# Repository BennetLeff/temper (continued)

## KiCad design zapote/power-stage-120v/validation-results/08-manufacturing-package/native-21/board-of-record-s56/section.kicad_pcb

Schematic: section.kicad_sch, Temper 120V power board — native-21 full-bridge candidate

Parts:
BR1: GBJ2510-F; Diode_Bridge_GBJ2510
C1, C2: R463N410050N1K; KEMET_R463N410000N1M_P22.50_ReviewOnly
C3, C4: DE1E3RA222MJ4BH01F; Murata_DE1E3RA222MA4BP01F_P10.0_Pad1.5_ReviewOnly
C5, C6: B32676G1905K000; TDK_B32656G0275J000_4Pin_P37.50_P20.30_ReviewOnly
C7, C14, C25, C28, C29, C32, C34, C35, C36, C37, C44, C45, C46, C47, C48, C49, C54, C61, C65, C70, C74, C75, C80, C81, C82, C87, C89, C131, C133, C134, C135, C139, C144, C153, C154, C155, C156, C157, C158, C159, C160, C161, C163, C168, C169, C170, C171, C172, C173, C174, C175, C176, C177, C178: CC0603KRX7R9BB104; C_0603_1608Metric
C8, C10, C15, C17: CC0805KRX7R9BB104; C_0805_2012Metric
C9, C16, C24, C26, C90, C91, C92, C93, C94, C95, C96, C97, C98, C99, C100, C102, C103, C104, C106, C107, C108, C132, C136, C140: CL32B106KBJNNNE; C_1210_3225Metric
C11, C18: GRM21BZ71E106KE15L; C_0805_2012Metric
C12, C13, C19, C20: CC1206JKNPOCBN102; C_1206_3216Metric
C21, C22, C23, C151, C152: B32643H8104J000; Bank_Film_DualPitch_P22.5_P27.5_Radial
C27, C31, C33, C66, C67, C68, C69, C76, C77, C78, C79, C83, C84, C85, C86, C164, C165, C166: C0603C102J5GACTU; C_0603_1608Metric
C30, C167: CL10C101JB8NNNC; C_0603_1608Metric
C38, C39, C40, C41: B32652A0104K000; TDK_B32652A0104K000_P15.00_ReviewOnly
C42, C43: GRM31C5C1H104JA01L; C_1206_3216Metric
C50, C51, C52, C53, C57, C58, C59, C60, C64: GRM188R71E105KA12D; C_0603_1608Metric
C55, C56, C62, C63: GRM1885C1H472JA01D; C_0603_1608Metric
C71, C72, C105, C109, C162: CL10C331JB8NNNC; C_0603_1608Metric
C110, C111, C112, C113, C114, C115, C116, C117, C118, C119, C120, C121, C122, C123, C124, C125: CL05B104KB54PNC; C_0402_1005Metric
C126, C127, C128, C129: 6SVPC220MV; CP_Elec_6.3x5.9
C145, C146, C147, C148, C149, C150: CL21B105KBFNNNE; C_0805_2012Metric
D3, D17: 30KPA150CA; P600_Axial_P12.70mm_ReviewOnly
D4, D5: BAS116H,115; D_SOD-123F
D6, D7, D8, D9: PMEG6030EP,115; D_SOD-128
D18, D19, D20: BAT54S-7-F; SOT-23
F1: KLDR025.TXP; Fuseholder_Clip-10.3x38mm_Littelfuse_125_Inline_P41.76x10.8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
F2: 3403.0279.23; Fuse_Schurter_UMT-H_15.4x5.35mm
J1: 1714971; Phoenix_MKDS-5-2-9.52_1714971
J2, J5: 7466004R; Wuerth_REDCUBE-SMT_WP-SMBU_7466004R
J3, J11: B2P3-VH(LF)(SN); JST_VH_B2P3-VH_1x02_P7.92mm_Vertical
J4: 0430451612; Molex_Micro-Fit_3.0_43045-1612_2x08_P3.00mm_Vertical
J6: 1704004; Phoenix_KDS3_1704004_1Pos_2Pin_ReviewOnly
L1: B82726S2243A020; B82726S2_ReviewOnly
PS2: MPM-20-24; Converter_ACDC_MeanWell_IRM-20-xx_THT
Q2, Q3, Q5, Q6: IPW65R018CFD7; TO-247-3_Vertical
R1, R2: 1206W4F1003T5E; R_1206_3216Metric
R3, R4, R146: RC1206FR-07220KL; R_1206_3216Metric
R5: CSS2H-2512R-1L00F; R_Shunt_Bourns_CSS2H-2512_Kelvin
R6, R14: 0603WAF1000T5E; R_0603_1608Metric
R7, R15, R62, R128, R135, R136, R138, R140, R142: 0603WAF1003T5E; R_0603_1608Metric
R9, R17, R133: RT0603BRD0749K9L; R_0603_1608Metric
R10, R12, R18, R20: PS122WF680JT4E; R_2512_6332Metric
R11, R13, R19, R21, R73, R76, R91, R109, R124: 0603WAF1002T5E; R_0603_1608Metric
R22, R23, R24, R25, R26, R27, R28, R29: RC1206FR-07470KL; R_1206_3216Metric
R30: RT0603BRD0715K8L; R_0603_1608Metric
R31: 0603WAF5601T5E; R_0603_1608Metric
R32, R36, R49, R50, R78, R80, R82, R84, R96, R98, R100, R102, R111, R113, R115, R117: RT0603BRD0710KL; R_0603_1608Metric
R33: RT0603BRD077K5L; R_0603_1608Metric
R34: RT0603BRD0716KL; R_0603_1608Metric
R35, R44, R45, R61, R86, R88, R93, R104, R106, R119, R121: RT0603BRD0711KL; R_0603_1608Metric
R37: RT0603BRD07140KL; R_0603_1608Metric
R38: 0603WAF0000T5E; R_0603_1608Metric
R39: RC1206FR-073RL; R_1206_3216Metric
R40, R41: RT0603BRD071KL; R_0603_1608Metric
R42: 1206W4F1001T5E; R_1206_3216Metric
R43, R46: RT0603BRD072K21L; R_0603_1608Metric
R47, R134: 0603WAF1001T5E; R_0603_1608Metric
R48: RT0603BRD07105KL; R_0603_1608Metric
R51, R52, R55, R56: RL1206FR-070R68L; R_1206_3216Metric
R53, R54, R57, R58: 1206W4F100KT5E; R_1206_3216Metric
R59, R63, R65: RC1206FR-072K2L; R_1206_3216Metric
R67, R68, R69, R70: RC1206FR-0716K5L; R_1206_3216Metric
R71, R72, R74, R75, R131: ERJ-PA3F4991V; R_0603_1608Metric
R77, R95, R110: RT0603BRD076K2L; R_0603_1608Metric
R79, R97, R112: RT0603BRD074K42L; R_0603_1608Metric
R81, R99, R114: RT0603BRD07750RL; R_0603_1608Metric
R83, R101, R116: RT0603BRD072K94L; R_0603_1608Metric
R85, R103, R118: RT0603BRD0790K9L; R_0603_1608Metric
R87, R105, R120: RT0603BRD07104KL; R_0603_1608Metric
R92, R94, R144: RT0603BRD0763K4L; R_0603_1608Metric
R125: 0603WAF3302T5E; R_0603_1608Metric
R127, R129, R137, R139, R141, R143: 0603WAF2702T5E; R_0603_1608Metric
R130: AC05000001507JAC00; R_Axial_Vishay_AC05_D7.5mm_P5.08mm_Vertical
R132: 0603WAF2200T5E; R_0603_1608Metric
R145: TNPW060311K7BEEA; R_0603_1608Metric
RV1: TMOV20RP175E; TMOV20RP_ReviewOnly
T1: CST3015-200ED; CST3015
U1, U2: 2EDR8259XXUMA1; SOIC16W_Isolated
U3, U37, U38, U39: TPS70950QDBVRQ1; SOT-23-5
U4: AMC1311BDWVR; SOIC-8_7.5x5.85mm_P1.27mm
U5: LM4050AEM3-2.5/NOPB; SOT-23
U6, U7, U10, U11, U12: TLV3201AIDBVR; SOT-23-5
U8: SN74LVC1G10DBVR; SOT-23-6
U9, U32: CA-IS3720HW; SOIC16W_DW0016B_HV
U13: SN74LVC1G332DBVR; SOT-23-6
U14: TPS3700DDCR; SOT-23-6
U15, U24, U40: SN74LVC1G17DBVR; SOT-23-5
U16, U18, U20: TLVH431BQDBZR; SOT-23
U17, U19, U21: TL431BQDBZR; SOT-23
U22, U23: SN74LVC1G00DBVR; SOT-23-5
U26: TPS7A4700RGWR; Texas_RGW0020A_VQFN-20-1EP_5x5mm_P0.65mm_EP3.15x3.15mm
U29, U30, U31: LM2901BIDR; SOIC-14_3.9x8.7mm_P1.27mm
U36: VOL628A-2X001T; VOL628A_LSOP4_ReviewOnly
U41, U42: R24C2T25/R-R; RECOM_SSOP-36_7.5x12.83mm_P0.65mm_ReviewOnly
U43, U44: ISO6721FBDR; SOIC-8_3.9x4.9mm_P1.27mm
U45, U46: SN74LVC1G132DBVR; SOT-23-5

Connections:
ac_l_in: F1.1 (p1), J1.1 (p1)
ac_n_in: C1.2 (p2), J1.2 (p2), L1.2 (p2), R2.2 (p2), RV1.2 (p2)
bias_good: R146.1 (p1), U22.2 (p2), U23.2 (p2), U40.4 (Y); also elsewhere on the board
bias_good_j4: J4.1 (p1), R146.2 (p2)
bias_ha-en: R62.2 (p2), R127.1 (p1), U41.4 (p4)
bias_ha-fbm: C71.1 (p1), R92.2 (p2), R93.1 (p1), U41.33 (p33), U41.34 (p34)
bias_ha-outa_nc: U43.2 (p2)
bias_ha.iso-p3: U41.3 (p3)
bias_ha.iso-p32: U41.32 (p32)
bias_ha.monitor-good: R109.2 (p2), U30.1 (OUT2), U30.2 (OUT1), U30.13 (OUT4), U30.14 (OUT3), U43.3 (p3)
bias_ha.monitor-halfref: R97.2 (p2), R98.1 (p1), U30.5 (IN1+), U30.6 (IN2-), U30.8 (IN3-), U30.11 (IN4+)
bias_ha.monitor-ldo_en: R140.2 (p2), R141.1 (p1), U38.3 (EN)
bias_ha.monitor-ov: C77.1 (p1), R101.2 (p2), R102.1 (p1), U30.4 (IN1-); also elsewhere on the board
bias_ha.monitor-ref: R63.2 (p2), R97.1 (p1), U19.1 (K), U19.2 (REF)
bias_ha.monitor-spanov: C79.1 (p1), R105.2 (p2), R106.1 (p1), U30.10 (IN4-); also elsewhere on the board
bias_ha.monitor-spanuv: C78.1 (p1), R103.2 (p2), R104.1 (p1), U30.9 (IN3+); also elsewhere on the board
bias_ha.monitor-uv: C76.1 (p1), R99.2 (p2), R100.1 (p1), U30.7 (IN2+); also elsewhere on the board
bias_ha.monitor-v5: C136.1 (p1), C157.1 (p1), R109.1 (p1), U38.5 (OUT), U43.1 (p1)
bias_ha.monitor.ldo5-nc: U38.4 (NC)
bias_ha.split-fb: R95.2 (p2), R96.1 (p1), U18.1 (REF)
bias_hb-en: R128.2 (p2), R129.1 (p1), U42.4 (p4)
bias_hb-fbm: C72.1 (p1), R61.1 (p1), R94.2 (p2), U42.33 (p33), U42.34 (p34)
bias_hb-outa_nc: U44.2 (p2)
bias_hb.iso-p3: U42.3 (p3)
bias_hb.iso-p32: U42.32 (p32)
bias_hb.monitor-good: R124.2 (p2), U31.1 (OUT2), U31.2 (OUT1), U31.13 (OUT4), U31.14 (OUT3), U44.3 (p3)
bias_hb.monitor-halfref: R112.2 (p2), R113.1 (p1), U31.5 (IN1+), U31.6 (IN2-), U31.8 (IN3-), U31.11 (IN4+)
bias_hb.monitor-ldo_en: R142.2 (p2), R143.1 (p1), U39.3 (EN)
bias_hb.monitor-ov: C84.1 (p1), R116.2 (p2), R117.1 (p1), U31.4 (IN1-); also elsewhere on the board
bias_hb.monitor-ref: R65.2 (p2), R112.1 (p1), U21.1 (K), U21.2 (REF)
bias_hb.monitor-spanov: C86.1 (p1), R120.2 (p2), R121.1 (p1), U31.10 (IN4-); also elsewhere on the board
bias_hb.monitor-spanuv: C85.1 (p1), R118.2 (p2), R119.1 (p1), U31.9 (IN3+); also elsewhere on the board
bias_hb.monitor-uv: C83.1 (p1), R114.2 (p2), R115.1 (p1), U31.7 (IN2+); also elsewhere on the board
bias_hb.monitor-v5: C140.1 (p1), C159.1 (p1), R124.1 (p1), U39.5 (OUT), U44.1 (p1)
bias_hb.monitor.ldo5-nc: U39.4 (NC)
bias_hb.split-fb: R110.2 (p2), R111.1 (p1), U20.1 (REF)
bias_ls-fb: R77.2 (p2), R78.1 (p1), U16.1 (REF)
blw_l: F2.2 (p2), R130.1 (p1)
blw_lr: J11.1 (p1), R130.2 (p2)
bus_fault: J4.10 (p10), U13.4 (Y); also elsewhere on the board
bus_fault_hot: U8.4 (Y), U9.4 (p4); also elsewhere on the board
bus_fault_iso: R134.1 (p1), U9.13 (p13)
bus_p: BR1.1 (PLUS), C5.1 (p1), C5.2 (p2), C6.1 (p1), C6.2 (p2), C12.1 (p1), C19.1 (p1), C38.1 (p1), C39.1 (p1), C40.1 (p1), C41.1 (p1), D3.1 (p1), Q2.2 (D), Q5.2 (D), R3.1 (p1), R26.1 (p1)
busbleed_mid: D3.2 (p2), D17.1 (p1), R3.2 (p2), R4.1 (p1)
coil_feed: J2.1, T1.2 (p2)
crbleed_1: R22.2 (p2), R23.1 (p1)
crbleed_2: R23.2 (p2), R24.1 (p1)
crbleed_3: R24.2 (p2), R25.1 (p1)
ct_mon: J4.14 (p14), R47.2 (p2); also elsewhere on the board
ct_oc_neg: U11.1 (OUT), U13.6 (C)
ct_oc_pos: U10.1 (OUT), U13.3 (B)
ct_ref_hi: R43.2 (p2), R44.1 (p1), U10.4 (INN)
ct_ref_lo: R45.2 (p2), R46.1 (p1), U11.3 (INP)
ct_s1: C42.1 (p1), R39.1 (p1), R42.1 (p1), T1.3 (p3)
ct_s2: C42.2 (p2), C43.1 (p1), R39.2 (p2), R40.2 (p2), R41.1 (p1), T1.4 (p4), U12.4 (INN)
ct_sense_mon: D4.2 (A), D5.1 (K), R42.2 (p2), R47.1 (p1), U10.3 (INP), U11.4 (INN), U12.3 (INP)
ct_zc: J4.13 (p13), U12.1 (OUT); also elsewhere on the board
hb.iso-nc2: U32.2 (p2)
hb.iso-nc5: U32.5 (p5)
hb.iso-nc6: U32.6 (p6)
hb.iso-nc8: U32.8 (p8)
hb.iso-nc10: U32.10 (p10)
hb.iso-nc11: U32.11 (p11)
hb.iso-nc12: U32.12 (p12)
hb.iso-nc15: U32.15 (p15)
hb_bufo: R132.1 (p1), U46.4 (p4)
hb_hold: C166.1 (p1), D19.2 (p2), R133.1 (p1), U40.2 (A)
hb_m: C164.2 (p2), C165.1 (p1)
hb_rc: C162.1 (p1), R131.2 (p2), U45.2 (p2)
hb_rx: U32.13 (p13), U46.2 (p2)
hb_s: C164.1 (p1), R132.2 (p2)
hb_tx: R131.1 (p1), U32.4 (p4), U45.4 (p4)
hb_x: C165.2 (p2), D19.3 (p3)
hot5: C26.1 (p1), C28.1 (p1), C32.1 (p1), C34.1 (p1), C35.1 (p1), C36.1 (p1), C48.1 (p1), C49.1 (p1), C149.1 (p1), R31.1 (p1), R48.1 (p1), R50.1 (p1), U3.5 (OUT), U4.1 (VDD1), U6.5 (VCC), U7.5 (VCC), U8.5 (VCC), U9.3 (p3), U14.5 (VDD), U15.5 (VCC); also elsewhere on the board
hot5_en: R136.2 (p2), R137.1 (p1), U3.3 (EN)
hot5_ok_hot: U8.6 (C), U15.4 (Y)
hot5_uv_raw: R50.2 (p2), U14.1 (OUTA), U14.6 (OUTB), U15.2 (A)
hot5_uv_sense: R48.2 (p2), R49.1 (p1), U14.3 (INA)
hsb_good: R135.2 (p2), U46.1 (p1)
hv_ret: BR1.4 (MINUS), C5.3 (p3), C5.4 (p4), C6.3 (p3), C6.4 (p4), C38.2 (p2), C39.2 (p2), C40.2 (p2), C41.2 (p2), D17.2 (p2), R4.2 (p2), R5.4 (p4)
l_f: C1.1 (p1), F1.2 (p2), L1.1 (p1), R1.1 (p1), RV1.1 (p1)
l_filt: BR1.2 (AC1), C2.1 (p1), C3.1 (p1), F2.1 (p1), J3.1 (p1), L1.4 (p4), R67.1 (p1)
ldo_nr: C64.1 (p1), U26.14 (p14)
led1: R68.2 (p2), U36.1 (p1)
led2: R69.1 (p1), U36.2 (p2)
leg_a-driver_dis: R73.2 (p2), U1.5 (p5), U22.4 (p4)
leg_a-gate_h: C55.1 (p1), D6.2 (p2), Q2.1 (G), R10.2 (p2), R11.1 (p1)
leg_a-gate_l: C56.1 (p1), D7.2 (p2), Q3.1 (G), R12.2 (p2), R13.1 (p1)
leg_a-off_h: D6.1 (p1), R53.1 (p1)
leg_a-off_l: D7.1 (p1), R54.1 (p1)
leg_a-out_h: R10.1 (p1), R53.2 (p2), U1.15 (p15)
leg_a-out_l: R12.1 (p1), R54.2 (p2), U1.10 (p10); also elsewhere on the board
leg_a-permit_gate: R6.2 (p2), R7.1 (p1), U22.1 (p1)
leg_a.bias_h-damp: C126.1 (p1), R51.2 (p2)
leg_a.bias_l-damp: C127.1 (p1), R52.2 (p2)
leg_a.driver-dt: R9.1 (p1), U1.6 (p6)
leg_a.driver-nc_7: U1.7 (p7)
leg_b-driver_dis: R76.2 (p2), U2.5 (p5), U23.4 (p4); also elsewhere on the board
leg_b-gate_h: C62.1 (p1), D8.2 (p2), Q5.1 (G), R18.2 (p2), R19.1 (p1)
leg_b-gate_l: C63.1 (p1), D9.2 (p2), Q6.1 (G), R20.2 (p2), R21.1 (p1)
leg_b-off_h: D8.1 (p1), R57.1 (p1)
leg_b-off_l: D9.1 (p1), R58.1 (p1)
leg_b-out_h: R18.1 (p1), R57.2 (p2), U2.15 (p15)
leg_b-out_l: R20.1 (p1), R58.2 (p2), U2.10 (p10)
leg_b-permit_gate: R14.2 (p2), R15.1 (p1), U23.1 (p1)
leg_b.bias_h-damp: C128.1 (p1), R55.2 (p2)
leg_b.bias_l-damp: C129.1 (p1), R56.2 (p2)
leg_b.driver-dt: R17.1 (p1), U2.6 (p6)
leg_b.driver-nc_7: U2.7 (p7)
leg_ret: C13.2 (p2), C20.2 (p2), C52.1 (p1), C53.1 (p1), C56.2 (p2), C59.1 (p1), C60.1 (p1), C63.2 (p2), C92.1 (p1), C93.1 (p1), C96.1 (p1), C97.1 (p1), C114.1 (p1), C115.1 (p1), C116.1 (p1), C117.1 (p1), C122.1 (p1), C123.1 (p1), C124.1 (p1), C125.1 (p1), Q3.3 (S), Q6.3 (S), R5.1 (p1), R13.2 (p2), R21.2 (p2), R52.1 (p1), R56.1 (p1), R72.2 (p2), R75.2 (p2), R77.1 (p1), R81.1 (p1), R83.1 (p1), U16.2 (K); also elsewhere on the board
line_zc: J4.16 (p16), U24.4 (Y)
line_zc.buffer-nc: U24.1 (NC)
line_zc_raw: R125.2 (p2), U24.2 (A), U36.4 (p4)
ls_v5: C132.1 (p1), C133.1 (p1), C158.1 (p1), C160.1 (p1), C161.1 (p1), R91.1 (p1), U32.3 (p3), U37.5 (OUT), U43.8 (p8), U44.8 (p8), U45.5 (p5)
mon_good_ha: D18.3 (p3), U43.6 (p6)
mon_good_hb: D20.2 (p2), U44.6 (p6)
monitor_ls-good: D18.1 (p1), D20.3 (p3), R91.2 (p2), U29.1 (OUT2), U29.2 (OUT1), U29.13 (OUT4), U29.14 (OUT3), U45.1 (p1)
monitor_ls-halfref: R79.2 (p2), R80.1 (p1), U29.5 (IN1+), U29.6 (IN2-), U29.8 (IN3-), U29.11 (IN4+)
monitor_ls-ldo_en: R138.2 (p2), R139.1 (p1), U37.3 (EN)
monitor_ls-ov: C67.1 (p1), R83.2 (p2), R84.1 (p1), U29.4 (IN1-)
monitor_ls-ref: R59.2 (p2), R79.1 (p1), U17.1 (K), U17.2 (REF)
monitor_ls-spanov: C69.1 (p1), R87.2 (p2), R88.1 (p1), U29.10 (IN4-); also elsewhere on the board
monitor_ls-spanuv: C68.1 (p1), R85.2 (p2), R86.1 (p1), U29.9 (IN3+); also elsewhere on the board
monitor_ls-uv: C66.1 (p1), R81.2 (p2), R82.1 (p1), U29.7 (IN2+); also elsewhere on the board
monitor_ls.ldo5-nc: U37.4 (NC)
n_filt: BR1.3 (AC2), C2.2 (p2), C4.1 (p1), J11.2 (p2), L1.3 (p3), PS2.2 (p2), R70.2 (p2)
n_ha: C10.2 (p2), C11.2 (p2), C50.2 (p2), C51.2 (p2), C71.2 (p2), C75.2 (p2), C76.2 (p2), C77.2 (p2), C78.2 (p2), C79.2 (p2), C80.2 (p2), C90.2 (p2), C91.2 (p2), C104.2 (p2), C110.2 (p2), C111.2 (p2), C112.2 (p2), C113.2 (p2), C126.2 (p2), C135.2 (p2), C136.2 (p2), C145.2 (p2), C157.2 (p2), R93.2 (p2), R96.2 (p2), R98.2 (p2), R100.2 (p2), R102.2 (p2), R104.2 (p2), R106.2 (p2), R141.2 (p2), U1.14 (p14), U18.3 (A), U19.3 (A), U30.12 (GND), U38.2 (GND), U41.19 (p19), U41.20 (p20), U41.21 (p21), U41.22 (p22), U41.23 (p23), U41.24 (p24), U41.25 (p25), U41.26 (p26), U41.27 (p27), U41.30 (p30), U41.31 (p31), U41.35 (p35), U41.36 (p36), U43.4 (p4); also elsewhere on the board
n_hb: C17.2 (p2), C18.2 (p2), C57.2 (p2), C58.2 (p2), C72.2 (p2), C82.2 (p2), C83.2 (p2), C84.2 (p2), C85.2 (p2), C86.2 (p2), C87.2 (p2), C94.2 (p2), C95.2 (p2), C108.2 (p2), C118.2 (p2), C119.2 (p2), C120.2 (p2), C121.2 (p2), C128.2 (p2), C139.2 (p2), C140.2 (p2), C147.2 (p2), C159.2 (p2), R61.2 (p2), R111.2 (p2), R113.2 (p2), R115.2 (p2), R117.2 (p2), R119.2 (p2), R121.2 (p2), R143.2 (p2), U2.14 (p14), U20.3 (A), U21.3 (A), U31.12 (GND), U39.2 (GND), U42.19 (p19), U42.20 (p20), U42.21 (p21), U42.22 (p22), U42.23 (p23), U42.24 (p24), U42.25 (p25), U42.26 (p26), U42.27 (p27), U42.30 (p30), U42.31 (p31), U42.35 (p35), U42.36 (p36), U44.4 (p4); also elsewhere on the board
n_ls: C8.2 (p2), C9.2 (p2), C15.2 (p2), C16.2 (p2), C24.2 (p2), C52.2 (p2), C53.2 (p2), C59.2 (p2), C60.2 (p2), C64.2 (p2), C65.2 (p2), C66.2 (p2), C67.2 (p2), C68.2 (p2), C69.2 (p2), C70.2 (p2), C74.2 (p2), C81.2 (p2), C92.2 (p2), C93.2 (p2), C96.2 (p2), C97.2 (p2), C98.2 (p2), C99.2 (p2), C100.2 (p2), C102.2 (p2), C103.2 (p2), C105.2 (p2), C106.2 (p2), C107.2 (p2), C109.2 (p2), C114.2 (p2), C115.2 (p2), C116.2 (p2), C117.2 (p2), C122.2 (p2), C123.2 (p2), C124.2 (p2), C125.2 (p2), C127.2 (p2), C129.2 (p2), C131.2 (p2), C132.2 (p2), C133.2 (p2), C146.2 (p2), C148.2 (p2), C158.2 (p2), C160.2 (p2), C161.2 (p2), C162.2 (p2), PS2.3 (p3), R78.2 (p2), R80.2 (p2), R82.2 (p2), R84.2 (p2), R86.2 (p2), R88.2 (p2), R127.2 (p2), R129.2 (p2), R139.2 (p2), U1.9 (p9), U2.9 (p9), U16.3 (A), U17.3 (A), U26.4 (p4), U26.5 (p5), U26.7 (p7), U26.8 (p8), U26.9 (p9), U26.10 (p10), U26.21 (p21), U29.12 (GND), U32.1 (p1), U32.7 (p7), U37.2 (GND), U41.1 (p1), U41.2 (p2), U41.5 (p5), U41.8 (p8), U41.9 (p9), U41.10 (p10), U41.11 (p11), U41.12 (p12), U41.13 (p13), U41.14 (p14), U41.15 (p15), U41.16 (p16), U41.17 (p17), U41.18 (p18), U42.1 (p1), U42.2 (p2), U42.5 (p5), U42.8 (p8), U42.9 (p9), U42.10 (p10), U42.11 (p11), U42.12 (p12), U42.13 (p13), U42.14 (p14), U42.15 (p15), U42.16 (p16), U42.17 (p17), U42.18 (p18), U43.5 (p5), U43.7 (p7), U44.5 (p5), U44.7 (p7), U45.3 (p3); also elsewhere on the board
ocp_kelvin_n: R5.3 (p3), R33.2 (p2)
ocp_kelvin_p: C25.2 (p2), C26.2 (p2), C27.2 (p2), C28.2 (p2), C30.2 (p2), C31.2 (p2), C32.2 (p2), C33.2 (p2), C34.2 (p2), C35.2 (p2), C36.2 (p2), C48.2 (p2), C49.2 (p2), C149.2 (p2), R5.2 (p2), R30.2 (p2), R35.2 (p2), R37.2 (p2), R49.2 (p2), R137.2 (p2), R145.2 (p2), U3.2 (GND), U4.3 (SHTDN), U4.4 (GND1), U5.2 (A), U6.2 (GND), U7.2 (GND), U8.2 (GND), U9.1 (p1), U9.7 (p7), U14.2 (GND), U15.3 (GND); also elsewhere on the board
ocp_node: C30.1 (p1), R32.2 (p2), R33.1 (p1), U6.3 (INP); also elsewhere on the board
ocp_ok_hot: U6.1 (OUT), U8.1 (A)
ocp_thresh: C31.1 (p1), R34.2 (p2), R35.1 (p1), U6.4 (INN)
ovp_ok_hot: U7.1 (OUT), U8.3 (B)
ovp_thresh: C33.1 (p1), R36.2 (p2), R37.1 (p1), U7.3 (INP)
p2: U26.2 (p2)
p6: U26.6 (p6)
p11: U26.11 (p11)
p12: U26.12 (p12)
p17: U26.17 (p17)
p18: U26.18 (p18)
p19: U26.19 (p19)
p_ha: C10.1 (p1), C11.1 (p1), C75.1 (p1), C80.1 (p1), C104.1 (p1), C135.1 (p1), C145.1 (p1), R63.1 (p1), R71.1 (p1), R92.1 (p1), R103.1 (p1), R105.1 (p1), R140.1 (p1), U1.16 (p16), U30.3 (VCC), U38.1 (IN), U41.28 (p28), U41.29 (p29); also elsewhere on the board
p_hb: C17.1 (p1), C18.1 (p1), C82.1 (p1), C87.1 (p1), C108.1 (p1), C139.1 (p1), C147.1 (p1), R65.1 (p1), R74.1 (p1), R94.1 (p1), R118.1 (p1), R120.1 (p1), R142.1 (p1), U2.16 (p16), U31.3 (VCC), U39.1 (IN), U42.28 (p28), U42.29 (p29); also elsewhere on the board
pe: C3.2 (p2), C4.2 (p2), J6.1 (p1), J6.2 (p2), R38.1 (p1)
permit: J4.9 (p9), R6.1 (p1), R14.1 (p1), R135.1 (p1); also elsewhere on the board
pwm_ha: J4.5 (p5), U1.1 (p1); also elsewhere on the board
pwm_hb: J4.7 (p7), U2.1 (p1); also elsewhere on the board
pwm_la: J4.6 (p6), U1.2 (p2); also elsewhere on the board
pwm_lb: J4.8 (p8), U2.2 (p2); also elsewhere on the board
r1mid: R67.2 (p2), R68.1 (p1)
r2mid: R69.2 (p2), R70.1 (p1)
ref25: R31.2 (p2), R32.1 (p1), R34.1 (p1), R36.1 (p1), R144.1 (p1), U5.1 (K); also elsewhere on the board
ref25_wd: R144.2 (p2), R145.1 (p1), U14.4 (INB)
res_a: C21.1 (p1), C22.1 (p1), C23.1 (p1), C151.1 (p1), C152.1 (p1), J5.1, R22.1 (p1)
selv_gnd: C7.2 (p2), C14.2 (p2), C29.2 (p2), C37.2 (p2), C43.2 (p2), C44.2 (p2), C45.2 (p2), C46.2 (p2), C47.2 (p2), C54.2 (p2), C61.2 (p2), C89.2 (p2), C134.2 (p2), C144.2 (p2), C150.2 (p2), C153.2 (p2), C154.2 (p2), C155.2 (p2), C156.2 (p2), C163.2 (p2), C166.2 (p2), C167.2 (p2), C168.2 (p2), C169.2 (p2), C170.2 (p2), C171.2 (p2), C172.2 (p2), C173.2 (p2), C174.2 (p2), C175.2 (p2), C176.2 (p2), C177.2 (p2), C178.2 (p2), D5.2 (A), D19.1 (p1), J4.2 (p2), J4.4 (p4), J4.15 (p15), R7.2 (p2), R9.2 (p2), R15.2 (p2), R17.2 (p2), R38.2 (p2), R41.2 (p2), R44.2 (p2), R46.2 (p2), R133.2 (p2), U1.4 (p4), U2.4 (p4), U4.5 (GND2), U9.9 (p9), U9.16 (p16), U10.2 (GND), U11.2 (GND), U12.2 (GND), U13.2 (GND), U22.3 (p3), U23.3 (p3), U24.3 (GND), U32.9 (p9), U32.16 (p16), U36.3 (p3), U40.3 (GND), U46.3 (p3); also elsewhere on the board
sw_a: C12.2 (p2), C13.1 (p1), C50.1 (p1), C51.1 (p1), C55.2 (p2), C90.1 (p1), C91.1 (p1), C110.1 (p1), C111.1 (p1), C112.1 (p1), C113.1 (p1), Q2.3 (S), Q3.2 (D), R11.2 (p2), R51.1 (p1), R71.2 (p2), R95.1 (p1), R99.1 (p1), R101.1 (p1), T1.1 (p1), U18.2 (K); also elsewhere on the board
sw_b: C19.2 (p2), C20.1 (p1), C21.2 (p2), C22.2 (p2), C23.2 (p2), C57.1 (p1), C58.1 (p1), C62.2 (p2), C94.1 (p1), C95.1 (p1), C118.1 (p1), C119.1 (p1), C120.1 (p1), C121.1 (p1), C151.2 (p2), C152.2 (p2), Q5.3 (S), Q6.2 (D), R19.2 (p2), R25.2 (p2), R55.1 (p1), R74.2 (p2), R110.1 (p1), R114.1 (p1), R116.1 (p1), U20.2 (K); also elsewhere on the board
tco_l: J3.2 (p2), PS2.1 (p1)
u_bias_flt-nc: U40.1 (NC)
u_hot5_schmitt-nc: U15.1 (NC)
u_iso-nc2: U9.2 (p2)
u_iso-nc5: U9.5 (p5)
u_iso-nc6: U9.6 (p6)
u_iso-nc8: U9.8 (p8)
u_iso-nc10: U9.10 (p10)
u_iso-nc11: U9.11 (p11)
u_iso-nc12: U9.12 (p12)
u_iso-nc15: U9.15 (p15)
u_ldo-nc: U3.4 (NC)
u_ref-nc: U5.3 (NC)
v3v3: C7.1 (p1), C14.1 (p1), C29.1 (p1), C37.1 (p1), C44.1 (p1), C45.1 (p1), C46.1 (p1), C47.1 (p1), C54.1 (p1), C61.1 (p1), C89.1 (p1), C134.1 (p1), C144.1 (p1), C150.1 (p1), C153.1 (p1), C154.1 (p1), C155.1 (p1), C156.1 (p1), C163.1 (p1), C168.1 (p1), C169.1 (p1), C170.1 (p1), C171.1 (p1), C172.1 (p1), C173.1 (p1), C174.1 (p1), C175.1 (p1), C176.1 (p1), C177.1 (p1), C178.1 (p1), D4.1 (K), J4.3 (V3V3_FROM_CONTROLLER), R40.1 (p1), R43.1 (p1), R45.1 (p1), R73.1 (p1), R76.1 (p1), R125.1 (p1), U1.3 (p3), U1.8 (p8), U2.3 (p3), U2.8 (p8), U4.8 (VDD2), U9.14 (p14), U10.5 (VCC), U11.5 (VCC), U12.5 (VCC), U13.5 (VCC), U22.5 (p5), U23.5 (p5), U24.5 (VCC), U32.14 (p14), U40.5 (VCC), U46.5 (p5); also elsewhere on the board
v15_ls: C8.1 (p1), C9.1 (p1), C15.1 (p1), C16.1 (p1), C24.1 (p1), C25.1 (p1), C65.1 (p1), C70.1 (p1), C99.1 (p1), C100.1 (p1), C131.1 (p1), C146.1 (p1), C148.1 (p1), R59.1 (p1), R72.1 (p1), R75.1 (p1), R85.1 (p1), R87.1 (p1), R136.1 (p1), R138.1 (p1), U1.11 (p11), U2.11 (p11), U3.1 (IN), U26.1 (p1), U26.3 (p3), U26.20 (p20), U29.3 (VCC), U37.1 (IN); also elsewhere on the board
v24_raw: C74.1 (p1), C81.1 (p1), C98.1 (p1), C102.1 (p1), C103.1 (p1), C105.1 (p1), C106.1 (p1), C107.1 (p1), C109.1 (p1), PS2.4 (p4), R62.1 (p1), R128.1 (p1), U26.13 (p13), U26.15 (p15), U26.16 (p16), U41.6 (p6), U41.7 (p7), U42.6 (p6), U42.7 (p7); also elsewhere on the board
vbus_n: J4.12 (p12), U4.6 (VOUTN)
vbus_p: J4.11 (p11), U4.7 (VOUTP)
vdiv_1: R26.2 (p2), R27.1 (p1)
vdiv_2: R27.2 (p2), R28.1 (p1)
vdiv_3: R28.2 (p2), R29.1 (p1)
vote_b_nc: D20.1 (p1)
vote_nc: D18.2 (p2)
vsense_in: C27.1 (p1), R29.2 (p2), R30.1 (p1), U4.2 (VINP), U7.4 (INN)
xbleed_mid: R1.2 (p2), R2.1 (p1)

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
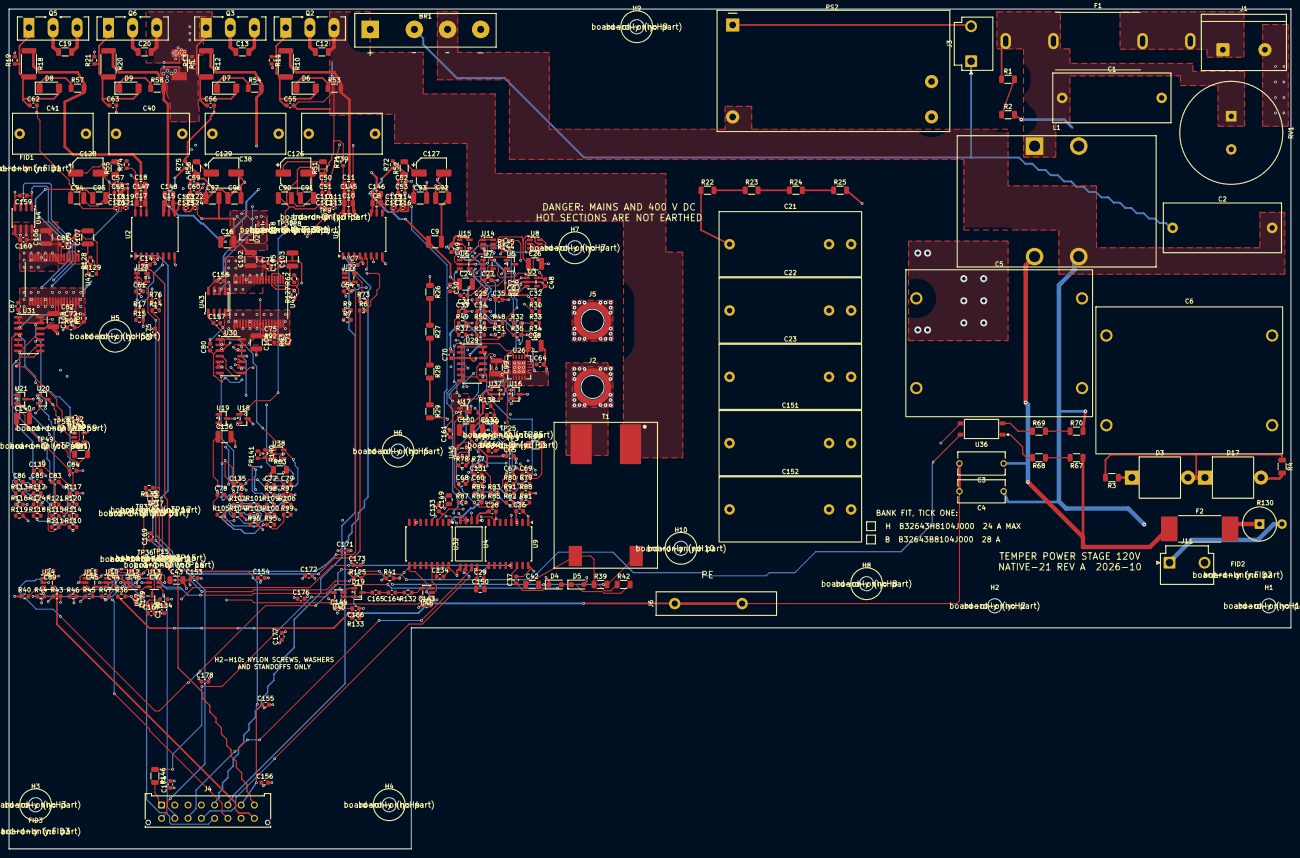
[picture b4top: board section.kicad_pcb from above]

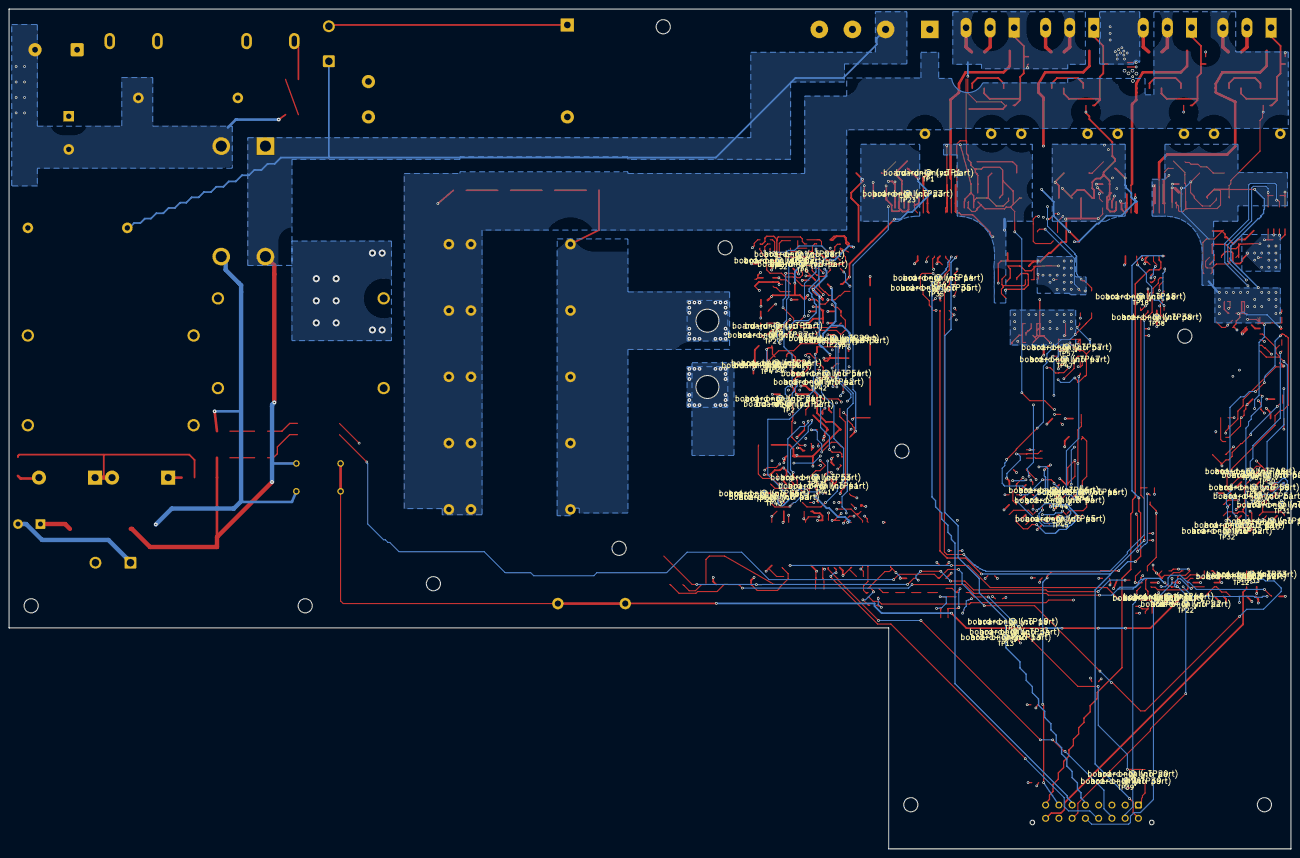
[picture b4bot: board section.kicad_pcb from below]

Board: 4 copper layers, 290.0 x 190.0 mm, 446 parts (47 on the bottom side), 145 nets.

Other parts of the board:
C179: CC0603KRX7R9BB104; C_0603_1608Metric
FID1, FID2, FID3: FIDUCIAL; Fiducial_1mm_Mask3mm
H1, H2: M3; MountingHole_3.2mm_M3
H3, H4, H5, H6, H7, H8, H9, H10: M3 NYLON ONLY; MountingHole_3.2mm_M3
TP1: leg_a-out_l; TestPoint_Pad_D1.0mm
TP2, TP23, TP26, TP53, TP54, TP55: n_ls; TestPoint_Pad_D1.0mm
TP3: v15_ls; TestPoint_Pad_D1.0mm
TP4: v24_raw; TestPoint_Pad_D1.0mm
TP5: ocp_node; TestPoint_Pad_D1.0mm
TP6: hot5; TestPoint_Pad_D1.0mm
TP7: bus_fault_hot; TestPoint_Pad_D1.0mm
TP8, TP56, TP57: n_ha; TestPoint_Pad_D1.0mm
TP9: p_ha; TestPoint_Pad_D1.0mm
TP10, TP58, TP59: n_hb; TestPoint_Pad_D1.0mm
TP11: p_hb; TestPoint_Pad_D1.0mm
TP12: v3v3; TestPoint_Pad_D1.0mm
TP13: pwm_ha; TestPoint_Pad_D1.0mm
TP14: pwm_la; TestPoint_Pad_D1.0mm
TP15: pwm_hb; TestPoint_Pad_D1.0mm
TP16: pwm_lb; TestPoint_Pad_D1.0mm
TP17: permit; TestPoint_Pad_D1.0mm
TP18: leg_b-driver_dis; TestPoint_Pad_D1.0mm
TP19: bias_good; TestPoint_Pad_D1.0mm
TP20: bus_fault; TestPoint_Pad_D1.0mm
TP21: ct_zc; TestPoint_Pad_D1.0mm
TP22: ct_mon; TestPoint_Pad_D1.0mm
TP24, TP25: leg_ret; TestPoint_Pad_D1.0mm
TP27, TP28, TP29: ocp_kelvin_p; TestPoint_Pad_D1.0mm
TP30: sw_a; TestPoint_Pad_D1.0mm
TP31, TP32: sw_b; TestPoint_Pad_D1.0mm
TP33, TP34, TP35, TP36, TP37, TP38, TP39, TP40: selv_gnd; TestPoint_Pad_D1.0mm
TP41: monitor_ls-uv; TestPoint_Pad_D1.0mm
TP42: monitor_ls-spanuv; TestPoint_Pad_D1.0mm
TP43: monitor_ls-spanov; TestPoint_Pad_D1.0mm
TP44: bias_ha.monitor-uv; TestPoint_Pad_D1.0mm
TP45: bias_ha.monitor-ov; TestPoint_Pad_D1.0mm
TP46: bias_ha.monitor-spanuv; TestPoint_Pad_D1.0mm
TP47: bias_ha.monitor-spanov; TestPoint_Pad_D1.0mm
TP48: bias_hb.monitor-uv; TestPoint_Pad_D1.0mm
TP49: bias_hb.monitor-ov; TestPoint_Pad_D1.0mm
TP50: bias_hb.monitor-spanuv; TestPoint_Pad_D1.0mm
TP51: bias_hb.monitor-spanov; TestPoint_Pad_D1.0mm
TP52: ref25; TestPoint_Pad_D1.0mm
U47: SN74LVC1G17DBVR; SOT-23-5

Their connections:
bias_good: TP19.1; also elsewhere on the board
bias_ha.monitor-ov: TP45.1; also elsewhere on the board
bias_ha.monitor-spanov: TP47.1; also elsewhere on the board
bias_ha.monitor-spanuv: TP46.1; also elsewhere on the board
bias_ha.monitor-uv: TP44.1; also elsewhere on the board
bias_hb.monitor-ov: TP49.1; also elsewhere on the board
bias_hb.monitor-spanov: TP51.1; also elsewhere on the board
bias_hb.monitor-spanuv: TP50.1; also elsewhere on the board
bias_hb.monitor-uv: TP48.1; also elsewhere on the board
bus_fault: TP20.1; also elsewhere on the board
bus_fault_hot: TP7.1; also elsewhere on the board
ct_mon: TP22.1; also elsewhere on the board
ct_zc: TP21.1; also elsewhere on the board
hot5: TP6.1; also elsewhere on the board
leg_a-out_l: TP1.1; also elsewhere on the board
leg_b-driver_dis: TP18.1; also elsewhere on the board
leg_ret: TP24.1, TP25.1; also elsewhere on the board
monitor_ls-spanov: TP43.1; also elsewhere on the board
monitor_ls-spanuv: TP42.1; also elsewhere on the board
monitor_ls-uv: TP41.1; also elsewhere on the board
n_ha: TP8.1, TP56.1, TP57.1; also elsewhere on the board
n_hb: TP10.1, TP58.1, TP59.1; also elsewhere on the board
n_ls: TP2.1, TP23.1, TP26.1, TP53.1, TP54.1, TP55.1; also elsewhere on the board
ocp_kelvin_p: TP27.1, TP28.1, TP29.1; also elsewhere on the board
ocp_node: TP5.1; also elsewhere on the board
p_ha: TP9.1; also elsewhere on the board
p_hb: TP11.1; also elsewhere on the board
permit: TP17.1; also elsewhere on the board
pwm_ha: TP13.1; also elsewhere on the board
pwm_hb: TP15.1; also elsewhere on the board
pwm_la: TP14.1; also elsewhere on the board
pwm_lb: TP16.1; also elsewhere on the board
ref25: TP52.1; also elsewhere on the board
selv_gnd: C179.2, TP33.1, TP34.1, TP35.1, TP36.1, TP37.1, TP38.1, TP39.1, TP40.1, U47.3; also elsewhere on the board
sw_a: TP30.1; also elsewhere on the board
sw_b: TP31.1, TP32.1; also elsewhere on the board
v3v3: C179.1, TP12.1, U47.5; also elsewhere on the board
v15_ls: TP3.1; also elsewhere on the board
v24_raw: TP4.1; also elsewhere on the board

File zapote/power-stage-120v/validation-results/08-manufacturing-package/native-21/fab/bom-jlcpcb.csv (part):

Comment,Designator,Footprint,LCSC Part #,Manufacturer Part Number,Mount,Assembly
1714971,J1,Phoenix_MKDS-5-2-9.52_1714971,C92145,1714971,THT,JLC (Extended)
KLDR025.TXP,F1,Fuseholder_Clip-10.3x38mm_Littelfuse_125_Inline_P41.76x10.80mm_Slot1.2x2.5mm_Horizontal,,KLDR025.TXP,THT,not soldered: the owner inserts the F1 cartridge into the hand-soldered clips after cleaning
TMOV20RP175E,RV1,TMOV20RP_ReviewOnly,,TMOV20RP175E,THT,"DNP at JLC: the owner hand-solders RV1 (form lead 2 in line, FOOTPRINTS F4; decision 2026-10-17)"
R463N410050N1K,"C1,C2",KEMET_R463N410000N1M_P22.50_ReviewOnly,C3299886,R463N410050N1K,THT,JLC (Extended); reserve by pre-order (JLC 46 against 40 on 2026-10-18); JLC hand-solders
1206W4F1003T5E,"R1,R2",R_1206_3216Metric,C17900,1206W4F1003T5E,SMD,JLC (Basic)
B82726S2243A020,L1,B82726S2_ReviewOnly,C7084710,B82726S2243A020,THT,"JLC (Extended), Global Sourcing (Mouser 62 / DigiKey 29); JLC hand-solders"
DE1E3RA222MJ4BH01F,"C3,C4",Murata_DE1E3RA222MA4BP01F_P10.0_Pad1.5_ReviewOnly,C7170908,DE1E3RA222MJ4BH01F,THT,JLC (Extended)
GBJ2510-F,BR1,Diode_Bridge_GBJ2510,,GBJ2510-F,THT,"DNP at JLC: the owner hand-solders BR1 before mains (bottom preheat >= 100 C; the only mains-to-bus path, left out on bench-bus boards, ASSEMBLY.md)"
B32676G1905K000,"C5,C6",TDK_B32656G0275J000_4Pin_P37.50_P20.30_ReviewOnly,C3802167,B32676G1905K000,THT,"JLC (Extended), Global Sourcing (DigiKey 547); JLC hand-solders"
RC1206FR-07220KL,"R3,R4,R146",R_1206_3216Metric,C130275,RC1206FR-07220KL,SMD,JLC (Extended); stock at survey: JLC 56239 / LCSC 54400
CSS2H-2512R-1L00F,R5,R_Shunt_Bourns_CSS2H-2512_Kelvin,C4175647,CSS2H-2512R-1L00F,SMD,JLC (Extended)
2EDR8259XXUMA1,"U1,U2",SOIC16W_Isolated,C17455725,2EDR8259XXUMA1,SMD,JLC (Extended)
CC0603KRX7R9BB104,"C7,C54,C14,C61,C25,C28,C29,C32,C34,C35,C36,C37,C44,C45,C46,C179,C47,C153,C154,C155,C156,C168,C169,C170,C171,C172,C173,C174,C175,C176,C177,C178,C48,C49,C65,C131,C70,C74,C75,C135,C80,C157,C158,C81,C82,C139,C87,C159,C160,C161,C133,C134,C163,C144,C89",C_0603_1608Metric,C14663,CC0603KRX7R9BB104,SMD,JLC (Basic)
0603WAF1000T5E,"R6,R14",R_0603_1608Metric,C22775,0603WAF1000T5E,SMD,JLC (Basic)
0603WAF1003T5E,"R7,R15,R136,R138,R62,R140,R128,R142,R135",R_0603_1608Metric,C25803,0603WAF1003T5E,SMD,JLC (Basic)
RT0603BRD0749K9L,"R9,R17,R133",R_0603_1608Metric,C705780,RT0603BRD0749K9L,SMD,JLC (Extended); stock at survey: JLC 184932 / LCSC 166300
CC0805KRX7R9BB104,"C8,C10,C15,C17",C_0805_2012Metric,C49678,CC0805KRX7R9BB104,SMD,JLC (Basic)
CL21B105KBFNNNE,"C146,C145,C148,C147,C149,C150",C_0805_2012Metric,C28323,CL21B105KBFNNNE,SMD,JLC (Basic)
CL32B106KBJNNNE,"C9,C90,C91,C92,C93,C16,C94,C95,C96,C97,C24,C26,C98,C99,C100,C132,C102,C103,C104,C136,C106,C107,C108,C140",C_1210_3225Metric,C138687,CL32B106KBJNNNE,SMD,JLC (Extended)
GRM21BZ71E106KE15L,"C11,C18",C_0805_2012Metric,C237493,GRM21BZ71E106KE15L,SMD,JLC (Extended)
GRM188R71E105KA12D,"C50,C51,C52,C53,C57,C58,C59,C60,C64",C_0603_1608Metric,C86020,GRM188R71E105KA12D,SMD,JLC (Extended); stock at survey: JLC 27921 / LCSC 24150
CL05B104KB54PNC,"C110,C111,C112,C113,C114,C115,C116,C117,C118,C119,C120,C121,C122,C123,C124,C125",C_0402_1005Metric,C307331,CL05B104KB54PNC,SMD,JLC (Basic)
RL1206FR-070R68L,"R51,R52,R55,R56",R_1206_3216Metric,C728510,RL1206FR-070R68L,SMD,JLC (Extended)
6SVPC220MV,"C126,C127,C128,C129",CP_Elec_6.3x5.9,C128504,6SVPC220MV,SMD,JLC (Extended)
ERJ-PA3F4991V,"R71,R72,R74,R75,R131",R_0603_1608Metric,C4036134,ERJ-PA3F4991V,SMD,JLC (Extended)
SN74LVC1G00DBVR,"U22,U23",SOT-23-5,C7826,SN74LVC1G00DBVR,SMD,JLC (Extended)
0603WAF1002T5E,"R73,R11,R13,R76,R19,R21,R91,R109,R124",R_0603_1608Metric,C25804,0603WAF1002T5E,SMD,JLC (Basic)
PS122WF680JT4E,"R10,R12,R18,R20",R_2512_6332Metric,C2793964,PS122WF680JT4E,SMD,JLC (Extended)
GRM1885C1H472JA01D,"C55,C56,C62,C63",C_0603_1608Metric,C85980,GRM1885C1H472JA01D,SMD,JLC (Extended)
"PMEG6030EP,115","D6,D7,D8,D9",D_SOD-128,C456127,"PMEG6030EP,115",SMD,JLC (Extended); stock at survey: JLC 13136 / LCSC 13136
1206W4F100KT5E,"R53,R54,R57,R58",R_1206_3216Metric,C17928,1206W4F100KT5E,SMD,JLC (Basic)
IPW65R018CFD7,"Q2,Q3,Q5,Q6",TO-247-3_Vertical,C3289047,IPW65R018CFD7,THT,"JLC (Extended), consigned: the single 120-piece DigiKey lot (ship 84; all 80 placements from the consigned stock, none from JLC's own); JLC hand-solders, package seated on the lead shoulders"
CC1206JKNPOCBN102,"C12,C13,C19,C20",C_1206_3216Metric,C113872,CC1206JKNPOCBN102,SMD,JLC (Extended)
CST3015-200ED,T1,CST3015,C50132500,CST3015-200ED,SMD,JLC (Extended); reserve by pre-order (JLC 64 against 20 on 2026-10-18)
7466004R,"J2,J5",Wuerth_REDCUBE-SMT_WP-SMBU_7466004R,C6708126,7466004R,SMD,"JLC (Extended), Global Sourcing (DigiKey 8,856); JLC places"
B32643H8104J000,"C21,C22,C23,C151,C152",Bank_Film_DualPitch_P22.5_P27.5_Radial,,B32643H8104J000,THT,"JLC (Extended), Global Sourcing (Mouser 1,736 / DigiKey 306); no public JLC number: select the private-library stock at the BOM step; JLC hand-solders it into the 22.5 mm holes, the five x 190.5 holes stay open; tick H"
RC1206FR-07470KL,"R22,R23,R24,R25,R26,R27,R28,R29",R_1206_3216Metric,C137273,RC1206FR-07470KL,SMD,JLC (Extended); stock at survey: JLC 121554 / LCSC 102400
B2P3-VH-H(LF)(SN),"J3,J11",JST_VH_B2P3-VH_1x02_P7.92mm_Vertical,C160900,B2P3-VH-H(LF)(SN),THT,"JLC (Extended); ordered as the grey JST B2P3-VH-H(LF)(SN) (source MPN B2P3-VH(LF)(SN)); JLC 5,610; JLC hand-solders"
3403.0279.23,F2,Fuse_Schurter_UMT-H_15.4x5.35mm,C3163739,3403.0279.23,SMD,"JLC (Extended), Global Sourcing (DigiKey 7,183, MOQ 1, read 2026-10-18); JLC places"
AC05000001507JAC00,R130,R_Axial_Vishay_AC05_D7.5mm_P5.08mm_Vertical,C1382388,AC05000001507JAC00,THT,JLC (Extended)
MPM-20-24,PS2,Converter_ACDC_MeanWell_IRM-20-xx_THT,C6675337,MPM-20-24,THT,JLC (Extended)
TPS70950QDBVRQ1,"U3,U37,U38,U39",SOT-23-5,C485909,TPS70950QDBVRQ1,SMD,JLC (Extended)
0603WAF2702T5E,"R137,R139,R127,R141,R129,R143",R_0603_1608Metric,C22967,0603WAF2702T5E,SMD,JLC (Basic)
RT0603BRD0715K8L,R30,R_0603_1608Metric,C861143,RT0603BRD0715K8L,SMD,JLC (Extended); stock at survey: JLC 7479 / LCSC 7460
C0603C102J5GACTU,"C27,C31,C33,C66,C67,C68,C69,C76,C77,C78,C79,C83,C84,C85,C86,C164,C165,C166",C_0603_1608Metric,C2181873,C0603C102J5GACTU,SMD,JLC (Extended); stock at survey: JLC 7526 / LCSC 7340
AMC1311BDWVR,U4,SOIC-8_7.5x5.85mm_P1.27mm,C783598,AMC1311BDWVR,SMD,JLC (Extended); stock at survey: JLC 1586 / LCSC 663
0603WAF5601T5E,R31,R_0603_1608Metric,C23189,0603WAF5601T5E,SMD,JLC (Basic)
LM4050AEM3-2.5/NOPB,U5,SOT-23,C2156518,LM4050AEM3-2.5/NOPB,SMD,JLC (Extended); reserve by pre-order (JLC 50 against 20)
RT0603BRD0710KL,"R32,R36,R49,R50,R78,R80,R82,R84,R96,R98,R100,R102,R111,R113,R115,R117",R_0603_1608Metric,C95204,RT0603BRD0710KL,SMD,JLC (Extended); stock at survey: JLC 2140811 / LCSC 383720
RT0603BRD077K5L,R33,R_0603_1608Metric,C728597,RT0603BRD077K5L,SMD,JLC (Extended)
CL10C101JB8NNNC,"C30,C167",C_0603_1608Metric,C14858,CL10C101JB8NNNC,SMD,JLC (Basic)
RT0603BRD0716KL,R34,R_0603_1608Metric,C326732,RT0603BRD0716KL,SMD,JLC (Extended)
RT0603BRD0711KL,"R35,R44,R45,R86,R88,R93,R104,R106,R61,R119,R121",R_0603_1608Metric,C728581,RT0603BRD0711KL,SMD,JLC (Extended)
TLV3201AIDBVR,"U6,U7,U10,U11,U12",SOT-23-5,C105188,TLV3201AIDBVR,SMD,JLC (Extended); stock at survey: JLC 30200 / LCSC 27302
RT0603BRD07140KL,R37,R_0603_1608Metric,C861125,RT0603BRD07140KL,SMD,JLC (Extended); stock at survey: JLC 9034 / LCSC 8960
SN74LVC1G10DBVR,U8,SOT-23-6,C403721,SN74LVC1G10DBVR,SMD,JLC (Extended); stock at survey: JLC 1525 / LCSC 1525
CA-IS3720HW,"U9,U32",SOIC16W_DW0016B_HV,C428883,CA-IS3720HW,SMD,JLC (Extended)
0430451612,J4,Molex_Micro-Fit_3.0_43045-1612_2x08_P3.00mm_Vertical,C491447,0430451612,THT,JLC (Extended); stock at survey: LCSC 7797 (2026-10-08 re-check; C17616543 had 0)
0603WAF0000T5E,R38,R_0603_1608Metric,C21189,0603WAF0000T5E,SMD,JLC (Basic)
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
